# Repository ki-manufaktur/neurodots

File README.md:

# NEURODOTS

This project is inspired by the 3D printed [4x4 Colour Dot Puzzle](https://www.instructables.com/4x4-Colour-Dot-Puzzle/) by Sebastian Coddington and featured in Hackaday: [Color Dot Puzzle Will Wrinkle Your Brain](https://hackaday.com/2022/02/12/color-dot-puzzle-will-wrinkle-your-brain/).

Neurodots is an electronic version of the color dot puzzle, utilizing a WS2812 RGB maze. The dots are shifted horizontally or vertically using switches on the sides of the maze to guide the dots into the solution configuration.

In addition to the core gameplay of solving the puzzle, the project includes a feature that displays solution hints, generated by a neural network running on the RP2040 using TensorFlow Lite for Microcontrollers (TFLM). This demonstrates an intriguing application of a small neural network, as the theoretical number of possible game states is approximately 1.19e+16.

Storing a recommended move for all these states would be far beyond the storage capacity of an embedded device, even with clever compression techniques. Moreover, even if storage wasn’t an issue, determining a near-optimal move to solve the puzzle is a non-trivial task. This challenge also applies to heuristic algorithms running on the device.

Thus, the training objective of the neural network was to find a policy that solves the puzzle using the minimum number of moves. By quantizing and deploying this model in the TFLM environment, solutions are generated in real-time, with a response time of approximately 1.4 seconds from state change to recommendation.

## Usage

https://github.com/user-attachments/assets/8f202e22-c553-46a4-99aa-1d21afb3c0ef

1. **Starting the Game**: Press the push button to start a new game. The LED matrix will display a shuffled maze according to the configured difficulty level.
2. **Interacting with the Game**: Use the slide switches to toggle the paths of the maze.
3. **Hints**: If you need help, press the push button to see the next move, as suggested by the device’s AI, on the LED matrix.
4. **Finishing the Game**: The game will automatically detect when the puzzle has been solved and will display a completion animation on the LED matrix.

## Installation

1. Clone the repository and navigate to the project folder:

   ```bash
   git clone https://github.com/ki-manufaktur/neurodots.git
   cd neurodots
   ```

2. Build the project using CMake. Ensure you have exported the PICO_SDK_PATH environment variable before proceeding:

   ```bash
   export PICO_SDK_PATH=/path/to/pico-sdk
   mkdir build
   cd build
   cmake ..
   make
   ```

3. Flash the compiled binary to your Raspberry Pi Pico:

   * Bridge JP1 to enable flashing
   * Copy the neurodots.uf2 file to the RP2040 flash drive to complete the installation.

## Configuration

Brightness and Level Settings: Hold down the push button while turning on the device to adjust the brightness and difficulty level using the slide switches. The settings will be saved to flash memory for future sessions.

### Difficulty Level

The difficulty level can be set using the horizontally aligned switch row, as shown below:
   ```
+-------------------------------+
| [ X ]  [ S2 ]  [ S1 ]  [ S0 ] |
|          ↑1      ↓0      ↑1   |
+-------------------------------+
   ```

In this example, the switch configuration (with the rightmost switch being the least significant bit, LSB) represents a  
Difficulty Level = (1 × 2^2) + (0 × 2^1) + (1 × 2^0) = 5

### Brightness

Similar to the difficulty level, the brightness of the LEDs can be set using the vertically aligned switch column, as shown below:

```
+-----+
| S3  |  (No Function)
+-----+
| S2  |  ↑1
+-----+
| S1  |  ↑1
+-----+
| S0  |  ↓0  (LSB)
+-----+
```

Where in this configuration the brightness level is 6.

## Contributing

We welcome contributions! Feel free to open issues for bug reports, feature requests, or any suggestions to improve the game. You can also submit pull requests to add new features or enhance existing functionality. Please ensure to follow any contribution guidelines provided.

## License

This project is dual-licensed:

   * The software is licensed under the GNU General Public License v3.0 (GPLv3).
   * The PCB designs and schematics are licensed under the Creative Commons Attribution-NonCommercial-ShareAlike (CC BY-NC-SA) license.

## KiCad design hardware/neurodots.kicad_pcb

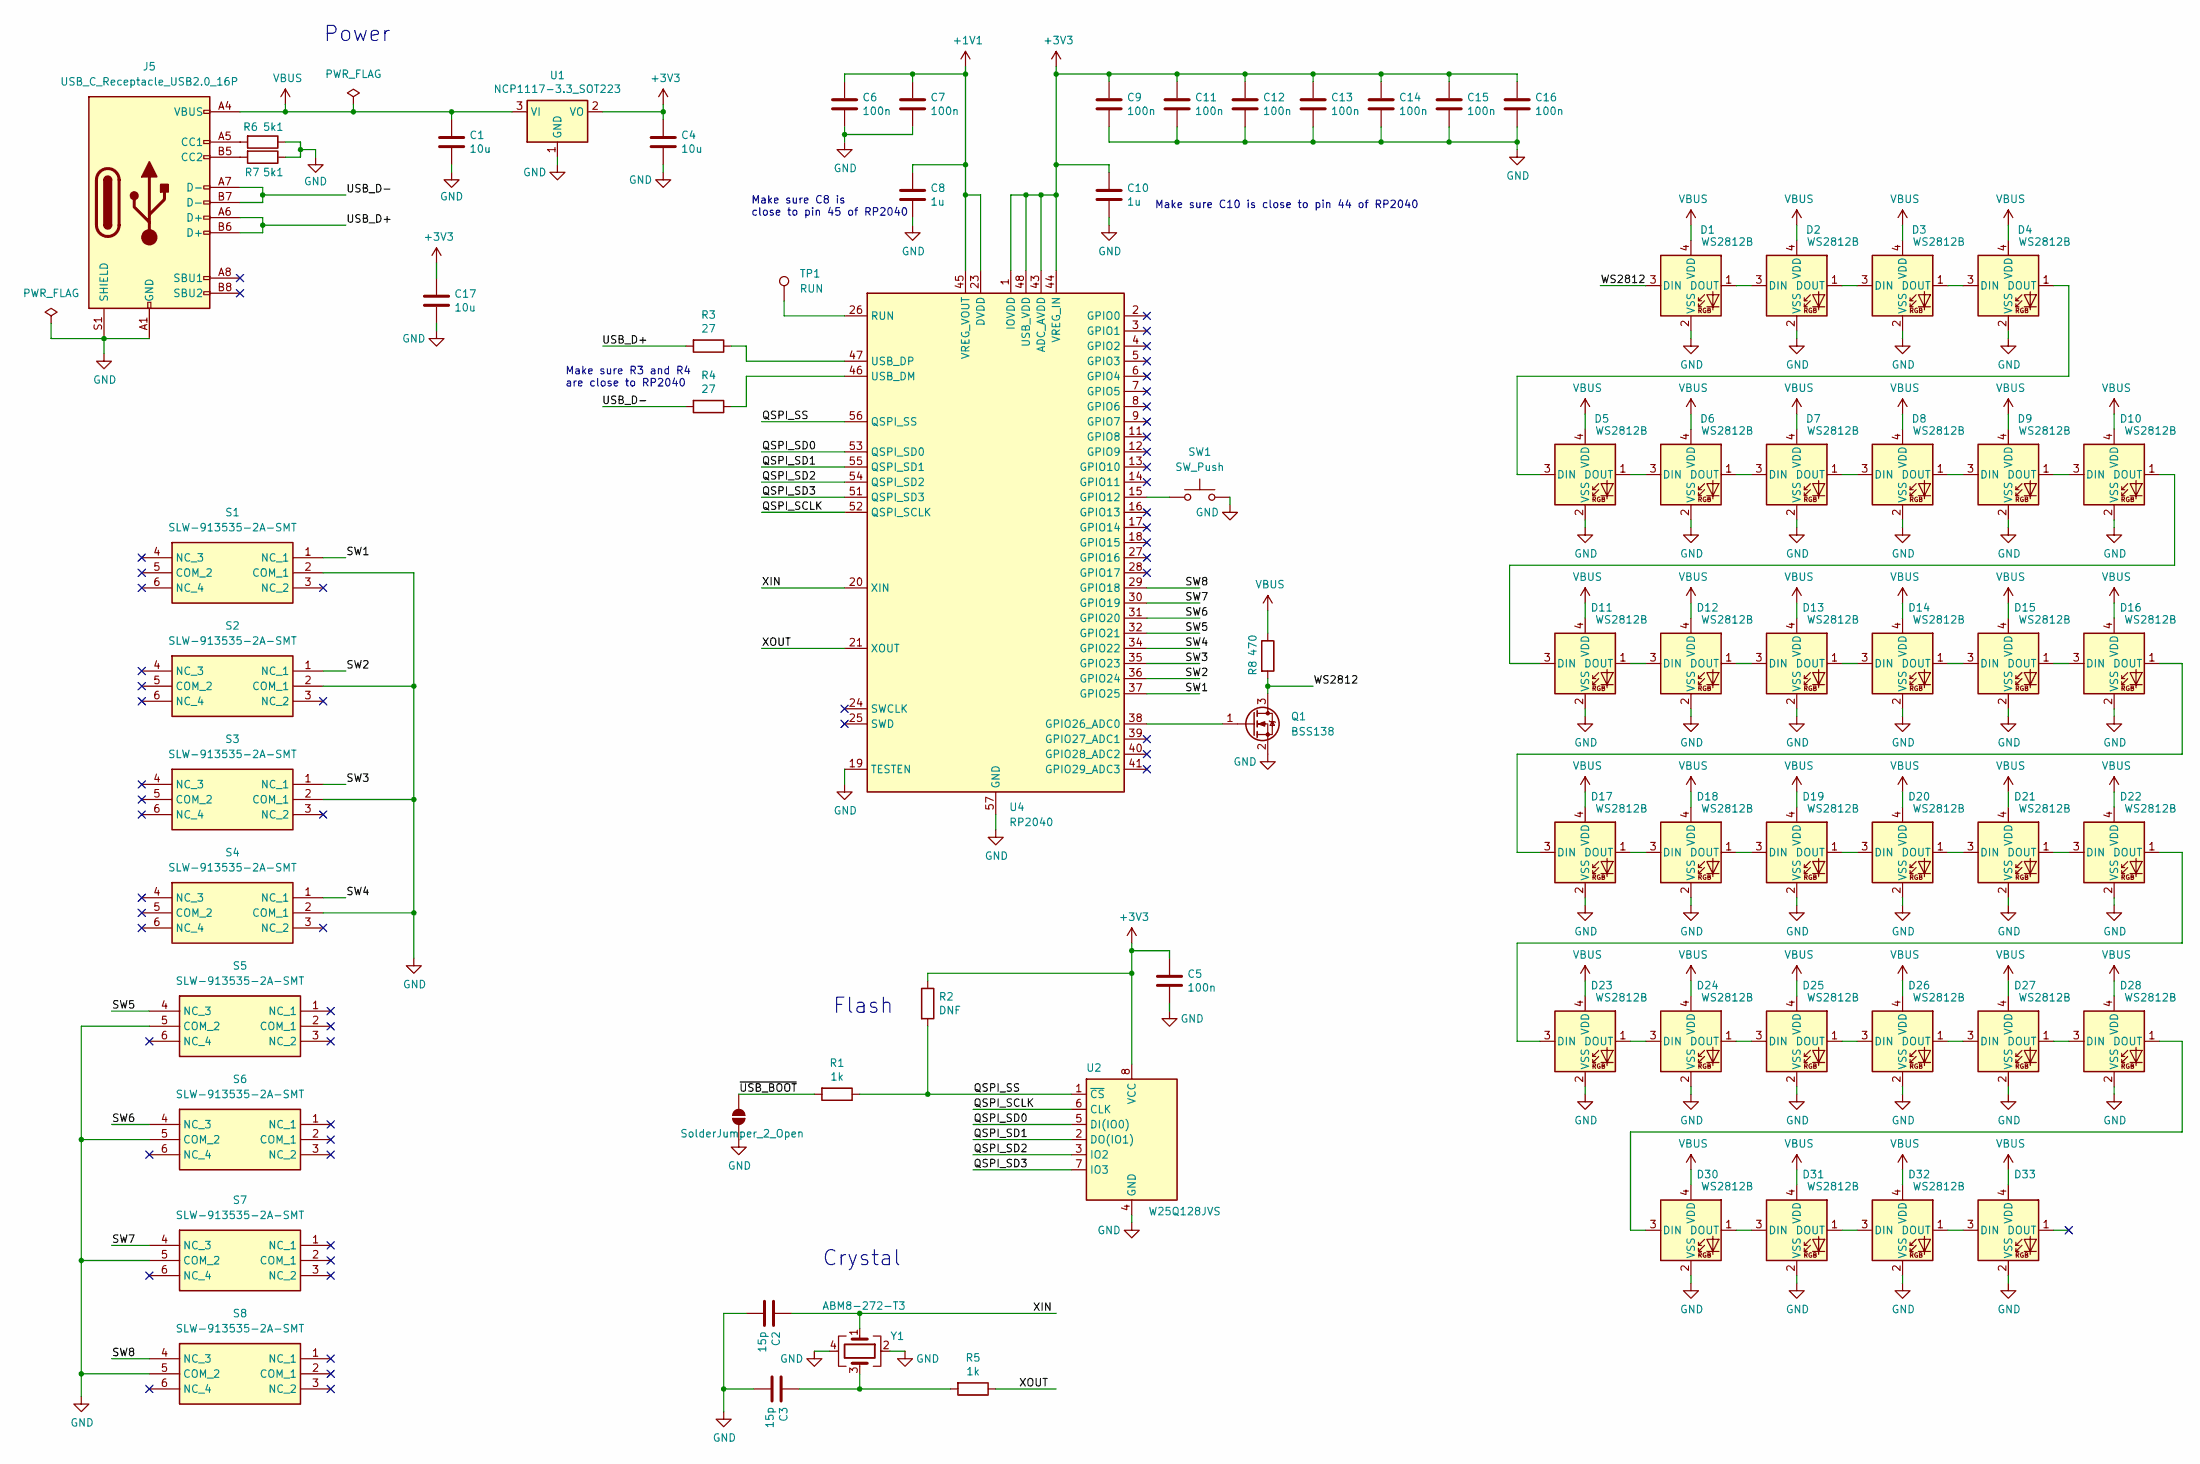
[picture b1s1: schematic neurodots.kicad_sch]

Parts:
C1, C4, C17: 10u; C_0805_2012Metric
C2, C3: 15p; C_0402_1005Metric
C5, C6, C7, C9, C11, C12, C13, C14, C15, C16: 100n; C_0402_1005Metric
C8, C10: 1u; C_0402_1005Metric
D1, D2, D3, D4, D5, D6, D7, D8, D9, D10, D11, D12, D13, D14, D15, D16, D17, D18, D19, D20, D21, D22, D23, D24, D25, D26, D27, D28, D30, D31, D32, D33: WS2812B; LED_WS2812B-Mini_PLCC4_3.5x3.5mm
J5: USB_C_Receptacle_USB2.0_16P; USB_C_Receptacle_GCT_USB4105-xx-A_16P_TopMnt_Horizontal
JP1: SolderJumper_2_Open; SolderJumper-2_P1.3mm_Open_TrianglePad1.0x1.5mm
Q1: BSS138; SOT-23
R1, R5: 1k; R_0402_1005Metric
R2: DNF; R_0402_1005Metric
R3, R4: 27; R_0402_1005Metric
R6, R7: 5k1; R_0402_1005Metric
R8: 470; R_0402_1005Metric
S1, S2, S3, S4, S5, S6, S7, S8: SLW-913535-2A-SMT; SLW9135352ASMT; Manufacturer_Part_Number SLW-913535-2A-SMT; Mouser Part Number 179-SLW-913535-2ASMT
SW1: SW_Push; SW_SPST_PTS645
TP1: RUN; TestPoint_Pad_D1.0mm
U1: NCP1117-3.3_SOT223; SOT-223-3_TabPin2
U2: W25Q128JVS; SOIC-8_5.23x5.23mm_P1.27mm
U4: RP2040; QFN-56-1EP_7x7mm_P0.4mm_EP3.2x3.2mm
Y1: ABM8-272-T3; Crystal_SMD_3225-4Pin_3.2x2.5mm

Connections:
+1V1: C6.1, C7.1, C8.1, U4.23 (DVDD), U4.45 (VREG_VOUT), U4.50 (DVDD)
+3V3: C4.1, C5.1, C9.1, C10.1, C11.1, C12.1, C13.1, C14.1, C15.1, C16.1, C17.1, R2.1, U1.2 (VO), U2.8 (VCC), U4.1 (IOVDD), U4.10 (IOVDD), U4.22 (IOVDD), U4.33 (IOVDD), U4.42 (IOVDD), U4.43 (ADC_AVDD), U4.44 (VREG_IN), U4.48 (USB_VDD), U4.49 (IOVDD)
/QSPI_SCLK: U2.6 (CLK), U4.52 (QSPI_SCLK)
/QSPI_SD0: U2.5 (DI(IO0)), U4.53 (QSPI_SD0)
/QSPI_SD1: U2.2 (DO(IO1)), U4.55 (QSPI_SD1)
/QSPI_SD2: U2.3 (IO2), U4.54 (QSPI_SD2)
/QSPI_SD3: U2.7 (IO3), U4.51 (QSPI_SD3)
/QSPI_SS: R1.1, R2.2, U2.1 (~CS), U4.56 (QSPI_SS)
/SW1: S1.1 (NC_1), U4.37 (GPIO25)
/SW2: S2.1 (NC_1), U4.36 (GPIO24)
/SW3: S3.1 (NC_1), U4.35 (GPIO23)
/SW4: S4.1 (NC_1), U4.34 (GPIO22)
/SW5: S5.4 (NC_3), U4.32 (GPIO21)
/SW6: S6.4 (NC_3), U4.31 (GPIO20)
/SW7: S7.4 (NC_3), U4.30 (GPIO19)
/SW8: S8.4 (NC_3), U4.29 (GPIO18)
/USB_D+: J5.A6 (D+), J5.B6 (D+), R3.2
/USB_D-: J5.A7 (D-), J5.B7 (D-), R4.2
/WS2812: D1.3 (DIN), Q1.3 (D), R8.2
/XIN: C2.1, U4.20 (XIN), Y1.1
/XOUT: R5.1, U4.21 (XOUT)
/~USB_BOOT: JP1.2 (B), R1.2
GND: C1.2, C2.2, C3.2, C4.2, C5.2, C6.2, C7.2, C8.2, C9.2, C10.2, C11.2, C12.2, C13.2, C14.2, C15.2, C16.2, C17.2, D1.2 (VSS), D2.2 (VSS), D3.2 (VSS), D4.2 (VSS), D5.2 (VSS), D6.2 (VSS), D7.2 (VSS), D8.2 (VSS), D9.2 (VSS), D10.2 (VSS), D11.2 (VSS), D12.2 (VSS), D13.2 (VSS), D14.2 (VSS), D15.2 (VSS), D16.2 (VSS), D17.2 (VSS), D18.2 (VSS), D19.2 (VSS), D20.2 (VSS), D21.2 (VSS), D22.2 (VSS), D23.2 (VSS), D24.2 (VSS), D25.2 (VSS), D26.2 (VSS), D27.2 (VSS), D28.2 (VSS), D30.2 (VSS), D31.2 (VSS), D32.2 (VSS), D33.2 (VSS), J5.A1 (GND), J5.A12 (GND), J5.B1 (GND), J5.B12 (GND), J5.S1 (SHIELD), JP1.1 (A), Q1.2 (S), R6.1, R7.1, S1.2 (COM_1), S2.2 (COM_1), S3.2 (COM_1), S4.2 (COM_1), S5.5 (COM_2), S6.5 (COM_2), S7.5 (COM_2), S8.5 (COM_2), SW1.2, U1.1 (GND), U2.4 (GND), U4.19 (TESTEN), U4.57 (GND), Y1.2, Y1.4
unnamed: C3.1, R5.2, Y1.3
unnamed: D1.1 (DOUT), D2.3 (DIN)
unnamed: D2.1 (DOUT), D3.3 (DIN)
unnamed: D3.1 (DOUT), D4.3 (DIN)
unnamed: D4.1 (DOUT), D5.3 (DIN)
unnamed: D5.1 (DOUT), D6.3 (DIN)
unnamed: D6.1 (DOUT), D7.3 (DIN)
unnamed: D7.1 (DOUT), D8.3 (DIN)
unnamed: D8.1 (DOUT), D9.3 (DIN)
unnamed: D9.1 (DOUT), D10.3 (DIN)
unnamed: D10.1 (DOUT), D11.3 (DIN)
unnamed: D11.1 (DOUT), D12.3 (DIN)
unnamed: D12.1 (DOUT), D13.3 (DIN)
unnamed: D13.1 (DOUT), D14.3 (DIN)
unnamed: D14.1 (DOUT), D15.3 (DIN)
unnamed: D15.1 (DOUT), D16.3 (DIN)
unnamed: D16.1 (DOUT), D17.3 (DIN)
unnamed: D17.1 (DOUT), D18.3 (DIN)
unnamed: D18.1 (DOUT), D19.3 (DIN)
unnamed: D19.1 (DOUT), D20.3 (DIN)
unnamed: D20.1 (DOUT), D21.3 (DIN)
unnamed: D21.1 (DOUT), D22.3 (DIN)
unnamed: D22.1 (DOUT), D23.3 (DIN)
unnamed: D23.1 (DOUT), D24.3 (DIN)
unnamed: D24.1 (DOUT), D25.3 (DIN)
unnamed: D25.1 (DOUT), D26.3 (DIN)
unnamed: D26.1 (DOUT), D27.3 (DIN)
unnamed: D27.1 (DOUT), D28.3 (DIN)
unnamed: D28.1 (DOUT), D30.3 (DIN)
unnamed: D30.1 (DOUT), D31.3 (DIN)
unnamed: D31.1 (DOUT), D32.3 (DIN)
unnamed: D32.1 (DOUT), D33.3 (DIN)
unnamed: J5.A5 (CC1), R6.2
unnamed: J5.B5 (CC2), R7.2
unnamed: Q1.1 (G), U4.38 (GPIO26_ADC0)
unnamed: SW1.1, U4.15 (GPIO12)
unnamed: TP1.1, U4.26 (RUN)
unnamed: R4.1, U4.46 (USB_DM)
unnamed: R3.1, U4.47 (USB_DP)
VBUS: C1.1, D1.4 (VDD), D2.4 (VDD), D3.4 (VDD), D4.4 (VDD), D5.4 (VDD), D6.4 (VDD), D7.4 (VDD), D8.4 (VDD), D9.4 (VDD), D10.4 (VDD), D11.4 (VDD), D12.4 (VDD), D13.4 (VDD), D14.4 (VDD), D15.4 (VDD), D16.4 (VDD), D17.4 (VDD), D18.4 (VDD), D19.4 (VDD), D20.4 (VDD), D21.4 (VDD), D22.4 (VDD), D23.4 (VDD), D24.4 (VDD), D25.4 (VDD), D26.4 (VDD), D27.4 (VDD), D28.4 (VDD), D30.4 (VDD), D31.4 (VDD), D32.4 (VDD), D33.4 (VDD), J5.A4 (VBUS), J5.A9 (VBUS), J5.B4 (VBUS), J5.B9 (VBUS), R8.1, U1.3 (VI)

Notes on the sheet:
Power
Crystal
Make sure C8 is close to pin 45 of RP2040
Make sure C10 is close to pin 44 of RP2040
Make sure R3 and R4 are close to RP2040
Flash

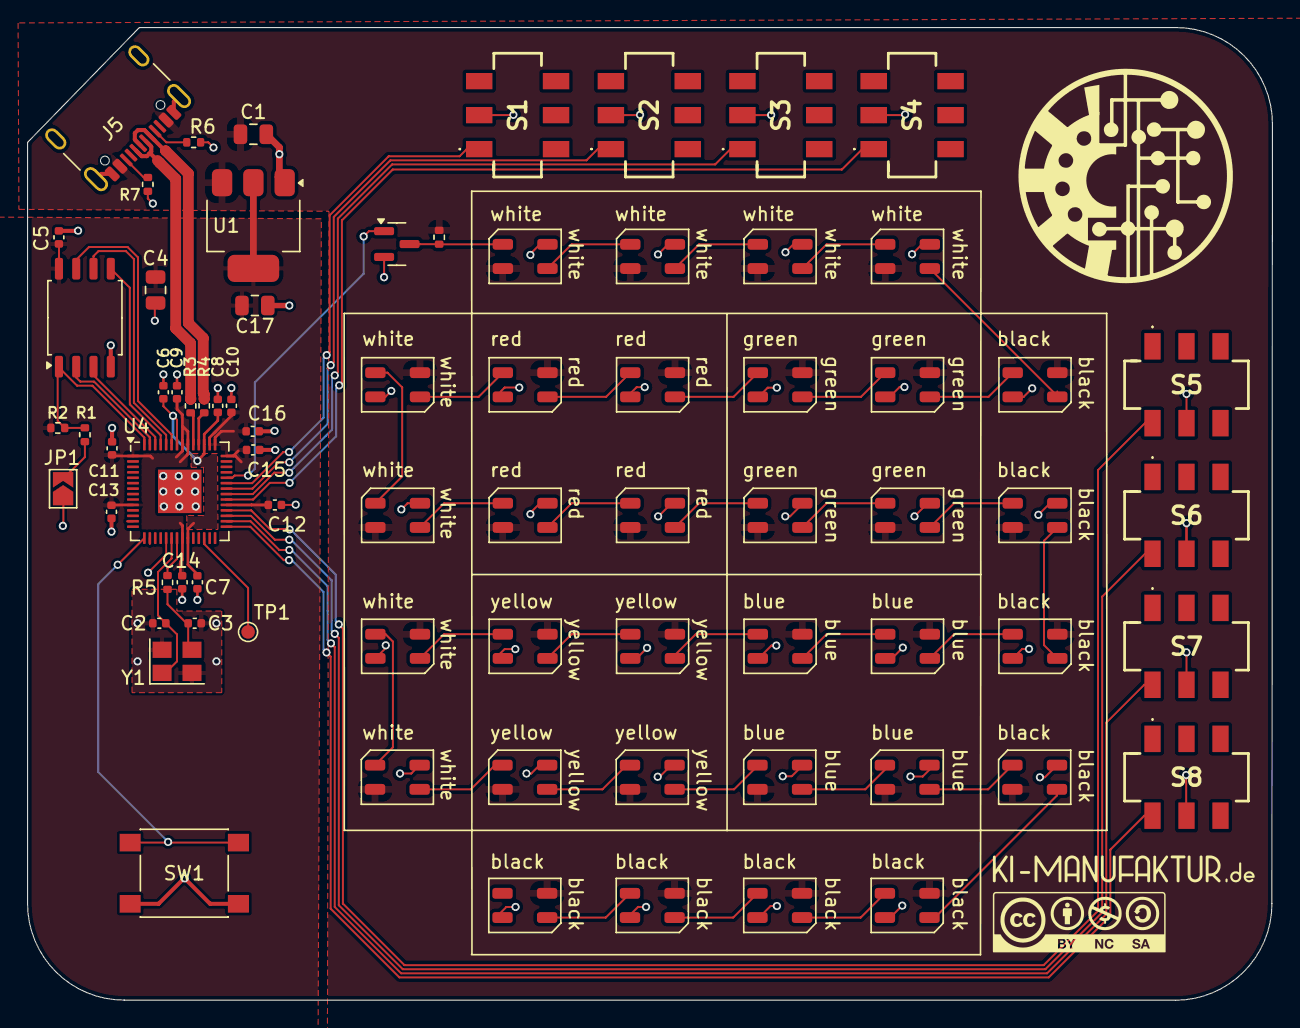
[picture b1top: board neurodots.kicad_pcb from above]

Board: 2 copper layers, 91.5 x 71.5 mm, 74 parts (0 on the bottom side), 63 nets.
